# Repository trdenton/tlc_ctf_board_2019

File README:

# TLC_CTF_Board

This board was created for the 2019 Long Con http://thelongcon.ca

This board contains two puzzles for participants of the CTF to complete.  The software for this device lives in a separate repository (TODO)

This board was designed in KiCAD.  Hardware and software design Copyright Troy Denton 2019

# License

The materials in this repo are released under the Creative Commons Attribution-ShareAlike 3.0 Unported License (CC BY-SA 3.0) https://creativecommons.org/licenses/by-sa/3.0/legalcode

# Credits

avr-isp-6 footprint courtesy of https://raw.githubusercontent.com/aspro648/KiCad/master/projects/Attiny/AttinyChallengeMisery/design_files/footprints.pretty/AVR-ISP-6.kicad_mod

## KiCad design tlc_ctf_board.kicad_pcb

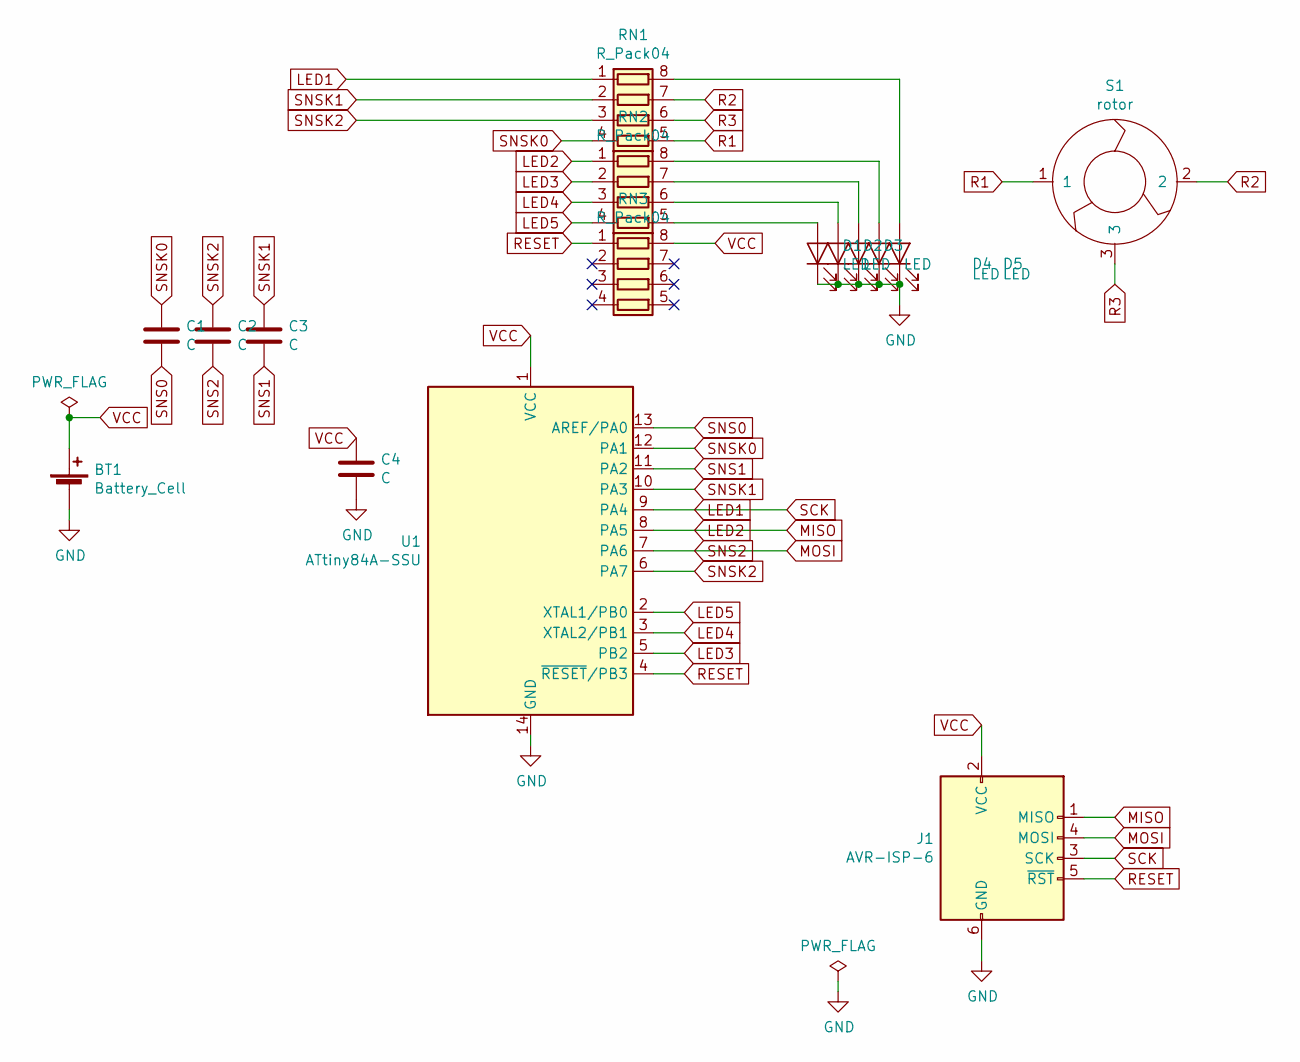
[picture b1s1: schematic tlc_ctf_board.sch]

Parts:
BT1: Battery_Cell; BatteryHolder_Keystone_3034_1x20mm
C1, C2, C3, C4: C; C_0603_1608Metric
D1, D2, D3, D4, D5: LED; LED_0603
J1: AVR-ISP-6
RN1, RN2, RN3: R_Pack04; r_array
S1: rotor; wheel_simple
U1: ATtiny84A-SSU; SOIC-14_3.9x8.7mm_P1.27mm

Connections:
GND: BT1.2 (-), C4.2, D1.1 (K), D2.1 (K), D3.1 (K), D4.1 (K), D5.1 (K), J1.6 (GND), U1.14 (GND)
LED1: J1.3 (SCK), RN1.1 (R1.1), U1.9 (PA4)
LED2: J1.1 (MISO), RN2.1 (R1.1), U1.8 (PA5)
LED3: RN2.2 (R2.1), U1.5 (PB2)
LED4: RN2.3 (R3.1), U1.3 (XTAL2/PB1)
LED5: RN2.4 (R4.1), U1.2 (XTAL1/PB0)
MOSI: C2.2, J1.4 (MOSI), U1.7 (PA6)
unnamed: D1.2 (A), RN2.5 (R4.2)
unnamed: D2.2 (A), RN2.6 (R3.2)
unnamed: D3.2 (A), RN2.7 (R2.2)
unnamed: D4.2 (A), RN2.8 (R1.2)
unnamed: D5.2 (A), RN1.8 (R1.2)
R1: RN1.5 (R4.2), S1.1
R2: RN1.7 (R2.2), S1.2
R3: RN1.6 (R3.2), S1.3
RESET: J1.5 (~RST), RN3.1 (R1.1), U1.4 (~RESET~/PB3)
SNS0: C1.2, U1.13 (AREF/PA0)
SNS1: C3.2, U1.11 (PA2)
SNSK0: C1.1, RN1.4 (R4.1), U1.12 (PA1)
SNSK1: C3.1, RN1.2 (R2.1), U1.10 (PA3)
SNSK2: C2.1, RN1.3 (R3.1), U1.6 (PA7)
VCC: BT1.1 (+), C4.1, J1.2 (VCC), RN3.8 (R1.2), U1.1 (VCC)

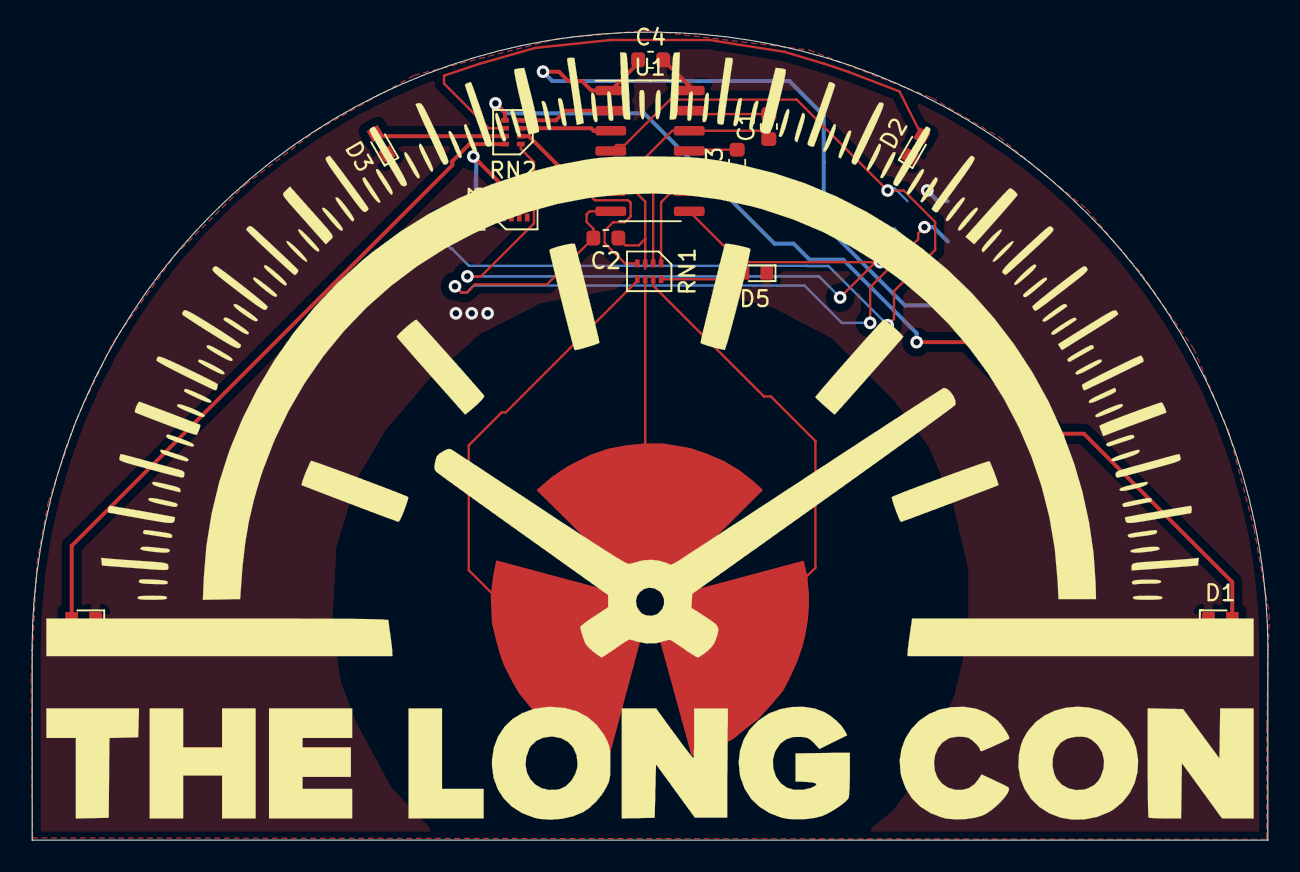
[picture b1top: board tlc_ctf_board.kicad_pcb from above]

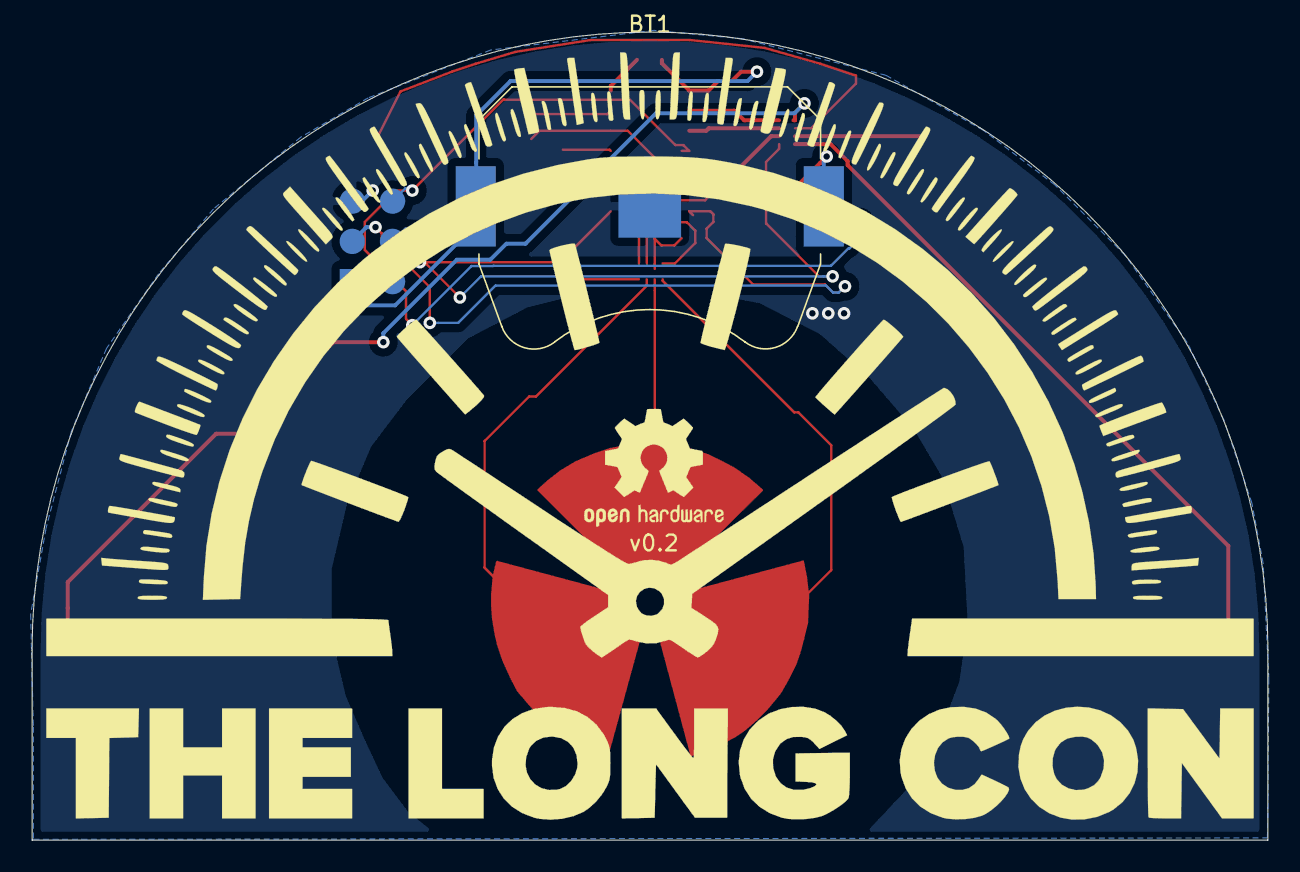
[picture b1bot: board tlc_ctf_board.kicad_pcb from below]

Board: 2 copper layers, 78.0 x 51.0 mm, 16 parts (2 on the bottom side), 22 nets.

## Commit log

2019-10-14 pcb mostly done
2019-10-14 moved programming header
2019-10-14 layed out state but need to adjust per qtouch wizeard
2019-10-14 fix connections per qtouch, reroute. switch to discrete caps
2019-10-18 adjust pads on battery, add oshw logo
2019-11-20 add last changes
2019-11-20 add readme
2019-11-20 use md
